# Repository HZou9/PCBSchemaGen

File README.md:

# PCBSchemaGen

LLM-based PCB schematic generation with automated topology verification.

# Installation

PCBSchemaGen requires:
- Python >= 3.10
- KiCad 9 (with pcbnew Python bindings)
- OpenAI-compatible API access

## Step 1: Install KiCad 9

Follow the official KiCad installation guide for your platform:

**https://www.kicad.org/download/**

After installation, verify KiCad and pcbnew:
```bash
kicad-cli --version
python3 -c "import pcbnew; print(pcbnew.GetBuildVersion())"
```

## Step 2: Install Python Dependencies

```bash
pip install openai pandas skidl networkx cairosvg Pillow
```

## Step 3: Environment Check

```bash
cd "sample design"
XDG_DATA_HOME=$(pwd)/../.xdg python3 run_samples_test.py
```

All 17 tasks should print `[PASS]`. If not, check your KiCad installation.

# Quick Start

```bash
cd task
XDG_DATA_HOME=$(pwd)/.. python3 run.py \
  --task_id 1 \
  --model gpt-4o \
  --api_key "YOUR_API_KEY" \
  --base_url https://openrouter.ai/api/v1
```

This generates a circuit for Task 1 (voltage divider).

# API Keys

Any OpenAI-compatible API works. We recommend [OpenRouter](https://openrouter.ai):
1. Create account at https://openrouter.ai
2. Get API key from dashboard
3. Use with `--base_url https://openrouter.ai/api/v1`

# Benchmark

- **Task definitions**: `benchmark.tsv` (23 tasks across 3 difficulty levels)
- **Reference designs**: `sample design/p*.py`
- **Component library**: `component.json`, `kg_component.json`
- **KiCad symbols/footprints**: `library/`

## Task Difficulty Levels

| Level | Tasks | Description |
|-------|-------|-------------|
| Easy | P1-P6 | Voltage dividers, LDOs, sensing circuits |
| Medium | P7-P16 | Half-bridge stages, gate drivers, isolated DC-DC |
| Hard | P17-P23 | Multi-switch converters (sync buck, DAB, LLC, 3-phase) |

# Example Output

The `example_output/` directory contains a successful run of Task 17 (Synchronous Buck Converter):

| File | Description |
|------|-------------|
| `attempt_1_skidl.py` | LLM-generated SKiDL code |
| `attempt_1.svg` | Circuit schematic visualization |
| `task_17_stats.json` | Run statistics (tokens, time, status) |
| `task_17_output.txt` | Full LLM output with chain-of-thought |
| `extracted_task_17.*` | Final artifacts (netlist, KiCad project) |

# Project Structure

```
PCBSchemaGen/
├── task/
│   ├── run.py                  # Single task runner
│   ├── run_feedback_trials.py  # Batch experiments
│   ├── topo/                   # Verification pipeline
│   └── prompt_template*.md     # LLM prompts
├── sample design/              # Ground truth implementations
├── library/                    # KiCad symbols & footprints
├── example_output/             # Example Task 17 output
├── benchmark.tsv               # Task definitions
├── component.json              # Component pin definitions
└── kg_component.json           # Component constraints
```

# Batch Experiments

To run multiple tasks with multiple trials:

```bash
cd task
XDG_DATA_HOME=$(pwd)/.. python3 run_feedback_trials.py \
  --task-range 1-16 \
  --trials 15 \
  --model gpt-4o \
  --api_key "YOUR_API_KEY" \
  --base_url https://openrouter.ai/api/v1 \
  --feedbacks full \
  --parallel-threads 8
```

Results are saved to `task/feedback_runs/`.

# Citation

If you find this work helpful, please cite our paper:

```bibtex
@misc{zou2026pcbschemagen,
      title={PCBSchemaGen: Constraint-Guided Schematic Design via LLM for Printed Circuit Boards (PCB)}, 
      author={Huanghaohe Zou and Peng Han and Emad Nazerian and Alex Q. Huang},
      year={2026},
      eprint={2602.00510},
      archivePrefix={arXiv},
      primaryClass={cs.AI},
      url={[https://arxiv.org/abs/2602.00510](https://arxiv.org/abs/2602.00510)}, 
}

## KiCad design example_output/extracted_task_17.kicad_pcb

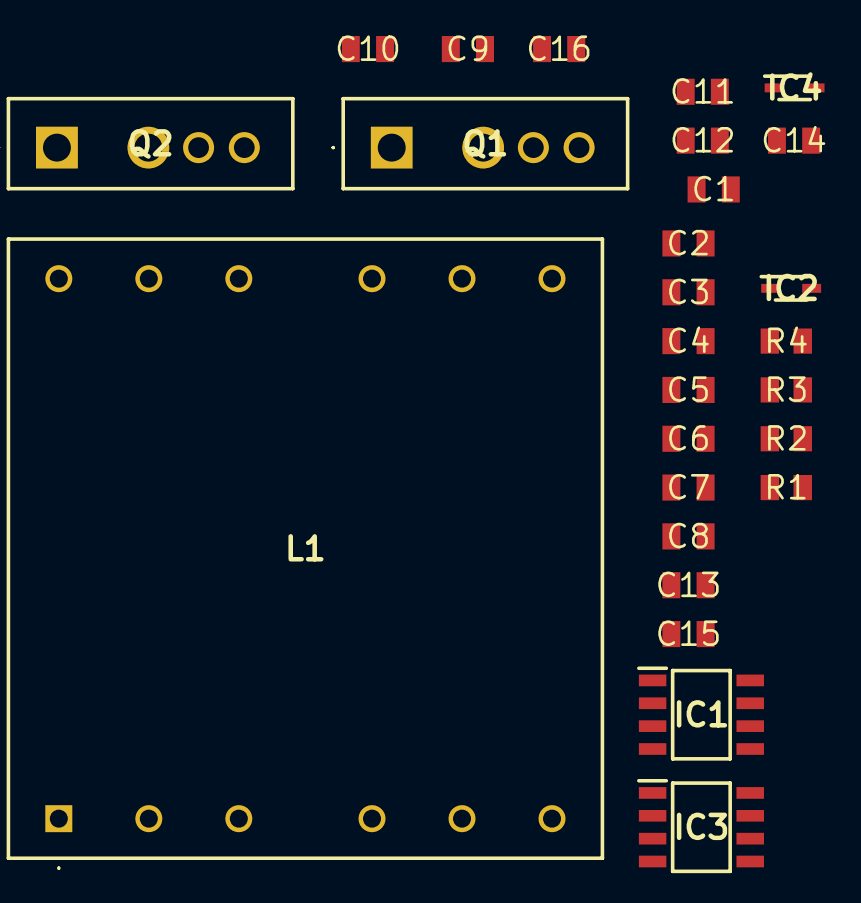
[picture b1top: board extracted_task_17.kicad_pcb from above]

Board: 2 copper layers, 27 parts (0 on the bottom side), 16 nets, no tracks yet.

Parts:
C1, C2, C3, C4, C5, C6, C7, C8, C13, C15: 100nF; C_0805
C9, C10, C11, C12: 22uF; C_0805
C14, C16: 1uF; C_0805
IC1, IC3: UCC5390E
IC2, IC4: D; BAT165
L1: Inductor_power
Q1, Q2: IMZA65R015M2H
R1, R3: 10; R_0805
R2, R4: 4.7; R_0805

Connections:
GND_PRI: C13.2, C15.2, IC1.3, IC1.4, IC3.3, IC3.4
KS_HS: C14.2, IC1.7, Q1.3
KS_LS: C16.2, IC3.7, Q2.3
unnamed: IC1.6, IC2.1, R1.1
unnamed: Q1.4, R1.2, R2.2
unnamed: IC2.2, R2.1
unnamed: IC3.6, IC4.1, R3.1
unnamed: Q2.4, R3.2, R4.2
unnamed: IC4.2, R4.1
PGND: C1.2, C2.2, C3.2, C4.2, C5.2, C6.2, C7.2, C8.2, C9.2, C10.2, C11.2, C12.2, Q2.2
VCC_12V: C13.1, C15.1, IC1.1, IC3.1
VDD_HS: C14.1, IC1.5
VDD_LS: C16.1, IC3.5
VIN: C1.1, C2.1, C3.1, C4.1, C5.1, C6.1, C7.1, C8.1, Q1.1
VOUT: C9.1, C10.1, C11.1, C12.1, L1.7, L1.8, L1.9, L1.10, L1.11, L1.12
VSW: L1.1, L1.2, L1.3, L1.4, L1.5, L1.6, Q1.2, Q2.1

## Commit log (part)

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2026-02-09 Add citation section to README
    Added citation for PCBSchemaGen paper.
